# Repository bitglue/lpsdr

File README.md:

# LPSDR

A low performance software defined radio.

Inspired by [HPSDR](http://openhpsdr.org/), except cheaper. Aims to cover HF
bands 160 to 10 meters.

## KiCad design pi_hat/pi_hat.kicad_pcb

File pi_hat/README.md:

# Dual SDR HAT for Raspberry Pi

- Covers all of HF, and probably a little bit of VHF too.
- Two RF inputs, can be tuned independently or coherently.
- LO generated by Si5351. Four outputs are used by the board, the other 4 are
  available on a header.
- [TLV320ADC5140 ADC](http://www.ti.com/lit/ds/symlink/tlv320adc5140.pdf),
  interfaces with Rasberry Pi via I²S.
- Perfboard area for stuff.

The board includes no filters but there is a header where they could be added.

## History

### v0.1 2020-05-14

Initial prototype. Don't know if it works yet.

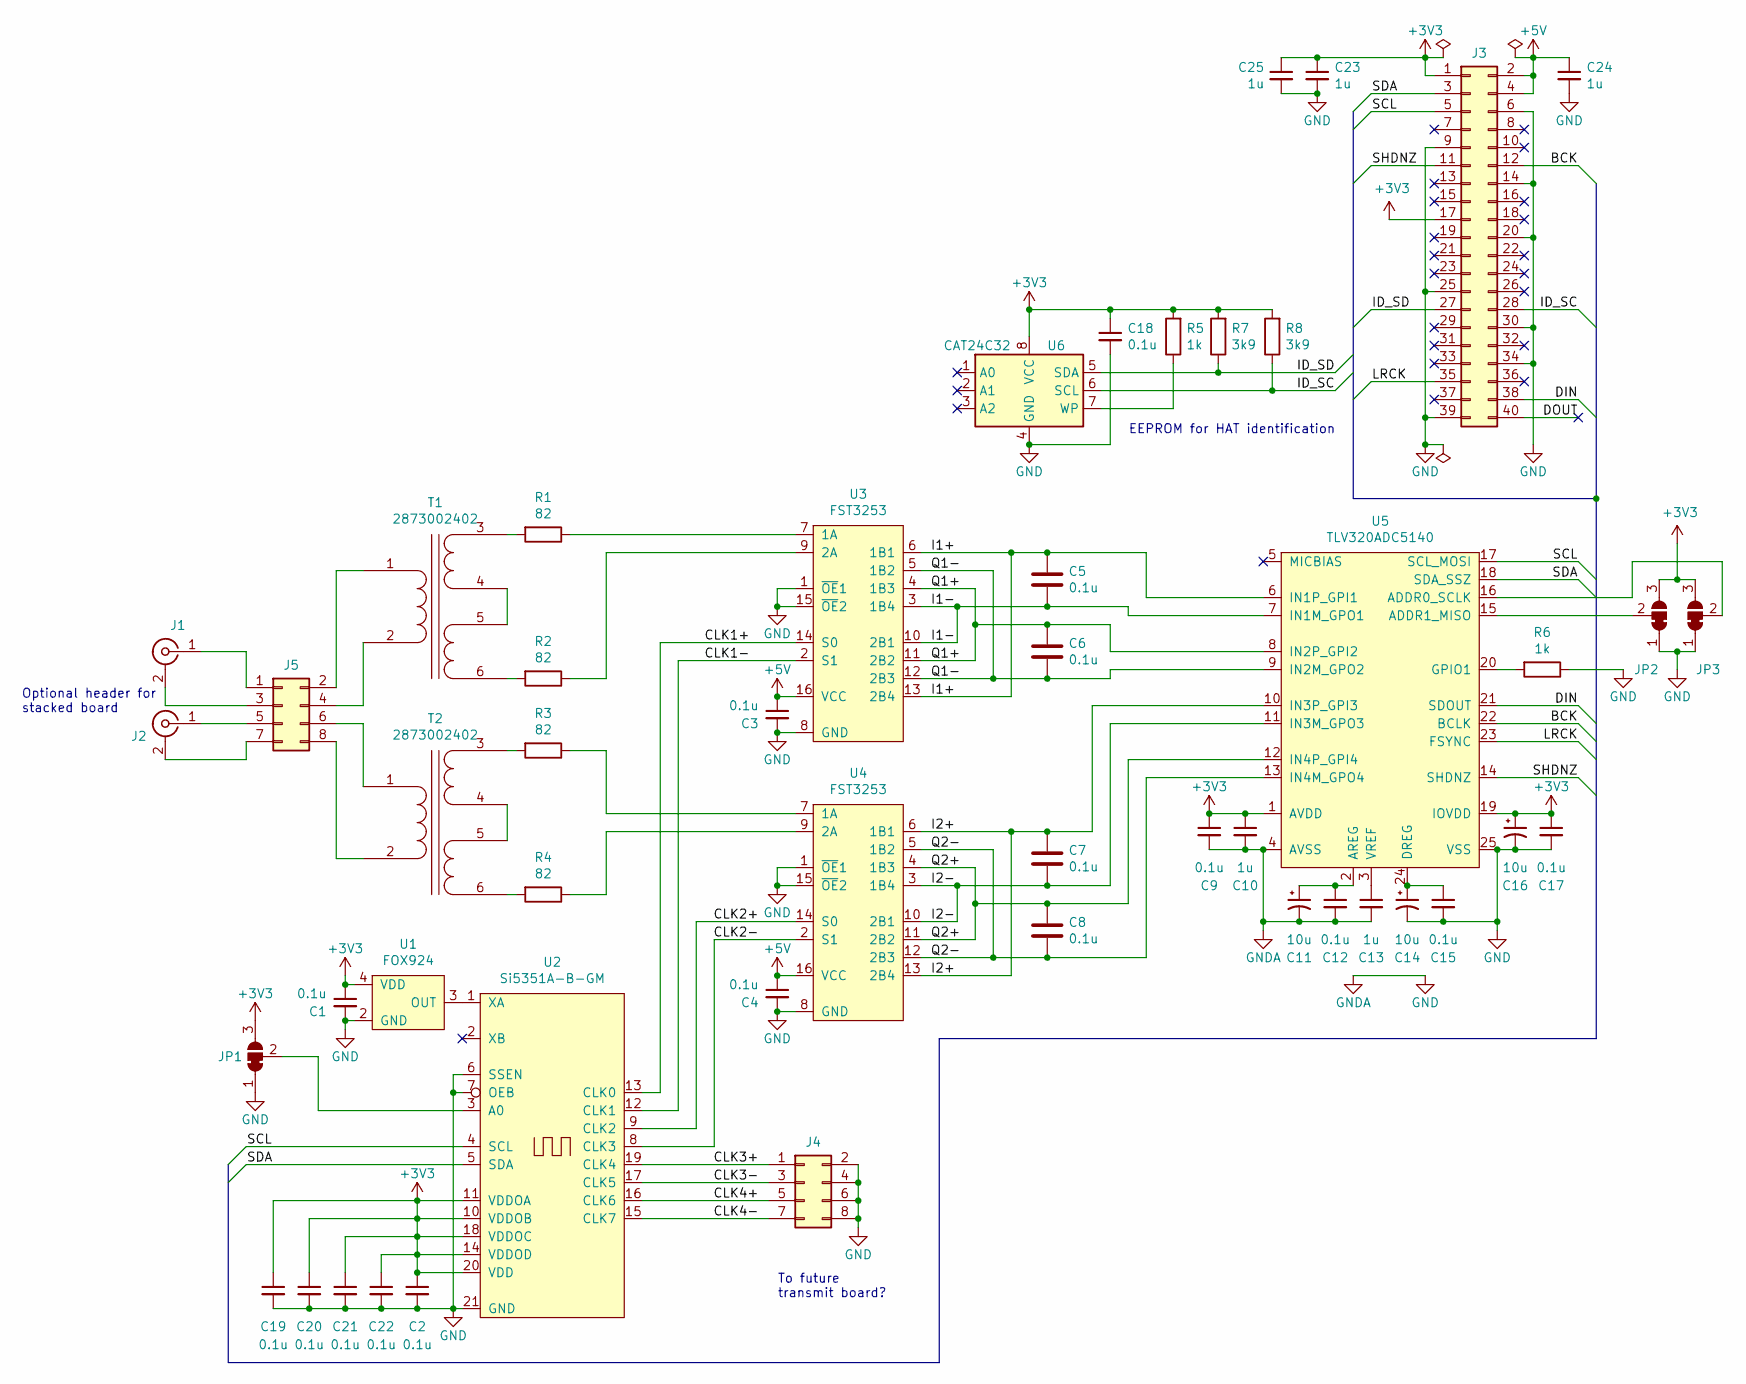
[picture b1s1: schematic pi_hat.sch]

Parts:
C1, C2, C3, C4, C5, C6, C7, C8, C9, C12, C15, C17, C18, C19, C20, C21, C22: 0.1u; C_1206_3216Metric_Pad1.42x1.75mm_HandSolder; mpn C1206C104M5RAC
C10, C13, C23, C24, C25: 1u; C_1206_3216Metric_Pad1.42x1.75mm_HandSolder; mpn C1206C105M3RACTU
C11, C14, C16: 10u; C_1206_3216Metric_Pad1.42x1.75mm_HandSolder; mpn C1206C106M3PAC
J1, J2: Conn_Coaxial; SMA_Samtec_SMA-J-P-H-ST-EM1_EdgeMount; mpn CON-SMA-EDGE-S
J3: Conn_02x20_Odd_Even; Pi_HAT; mpn SSQ-120-03-T-D
J4, J5: Conn_02x04_Odd_Even; PinHeader_2x04_P2.54mm_Vertical
JP1, JP2, JP3: SolderJumper_3_Bridged12; SolderJumper-3_P1.3mm_Bridged2Bar12_RoundedPad1.0x1.5mm
R1, R2, R3, R4: 82; R_1206_3216Metric_Pad1.42x1.75mm_HandSolder; mpn CR1206-FX-82R0ELF
R5, R6: 1k; R_1206_3216Metric_Pad1.42x1.75mm_HandSolder; mpn CRCW12061K00FKEBC
R7, R8: 3k9; R_1206_3216Metric_Pad1.42x1.75mm_HandSolder; mpn CRCW12063K90FKEAC
T1, T2: 2873002402; Binocular_Bifilar_Seconndary; mpn 2873002402
U1: FOX924; Crystal_SMD_EuroQuartz_MJ-4Pin_5.0x3.2mm_HandSoldering; mpn FT5HNBPK27.0-T1
U2: Si5351A-B-GM; QFN-20-1EP_4x4mm_P0.5mm_EP2.25x2.25mm; mpn SI5351A-B-GM
U3, U4: FST3253; SOIC-16_3.9x9.9mm_P1.27mm; mpn FST3253MTCX
U5: TLV320ADC5140; QFN-24-1EP_4x4mm_P0.5mm_EP2.7x2.7mm_ThermalVias; mpn TLV320ADC5140IRTWR
U6: CAT24C32; SOIC-8_3.9x4.9mm_P1.27mm; mpn CAT24C32WI-GT3

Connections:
+3V3: C1.1, C2.1, C9.1, C10.1, C16.1, C17.1, C18.1, C19.1, C20.1, C21.1, C22.1, C23.1, C25.1, J3.1, J3.17, JP1.3 (B), JP2.3 (B), JP3.3 (B), R5.2, R7.2, R8.2, U1.4 (VDD), U2.10 (VDDOB), U2.11 (VDDOA), U2.14 (VDDOD), U2.18 (VDDOC), U2.20 (VDD), U5.1 (AVDD), U5.19 (IOVDD), U6.8 (VCC)
+5V: C3.1, C4.1, C24.1, J3.2, J3.4, U3.16 (VCC), U4.16 (VCC)
/BCK: J3.12, U5.22 (BCLK)
/CLK1+: U2.13 (CLK0), U3.14 (S0)
/CLK1-: U2.12 (CLK1), U3.2 (S1)
/CLK2+: U2.9 (CLK2), U4.14 (S0)
/CLK2-: U2.8 (CLK3), U4.2 (S1)
/CLK3+: J4.1, U2.19 (CLK4)
/CLK3-: J4.3, U2.17 (CLK5)
/CLK4+: J4.5, U2.16 (CLK6)
/CLK4-: J4.7, U2.15 (CLK7)
/DIN: J3.38, U5.21 (SDOUT)
/DOUT: J3.40
/I1+: C5.1, U3.6 (1B1), U3.13 (2B4), U5.6 (IN1P_GPI1)
/I1-: C5.2, U3.3 (1B4), U3.10 (2B1), U5.7 (IN1M_GPO1)
/I2+: C7.1, U4.6 (1B1), U4.13 (2B4), U5.10 (IN3P_GPI3)
/I2-: C7.2, U4.3 (1B4), U4.10 (2B1), U5.11 (IN3M_GPO3)
/ID_SC: J3.28, R8.1, U6.6 (SCL)
/ID_SD: J3.27, R7.1, U6.5 (SDA)
/LRCK: J3.35, U5.23 (FSYNC)
/Q1+: C6.1, U3.4 (1B3), U3.11 (2B2), U5.8 (IN2P_GPI2)
/Q1-: C6.2, U3.5 (1B2), U3.12 (2B3), U5.9 (IN2M_GPO2)
/Q2+: C8.1, U4.4 (1B3), U4.11 (2B2), U5.12 (IN4P_GPI4)
/Q2-: C8.2, U4.5 (1B2), U4.12 (2B3), U5.13 (IN4M_GPO4)
/SCL: J3.5, U2.4 (SCL), U5.17 (SCL_MOSI)
/SDA: J3.3, U2.5 (SDA), U5.18 (SDA_SSZ)
/SHDNZ: J3.11, U5.14 (SHDNZ)
GND: C1.2, C2.2, C3.2, C4.2, C9.2, C10.2, C11.2, C12.2, C13.2, C14.2, C15.2, C16.2, C17.2, C18.2, C19.2, C20.2, C21.2, C22.2, C23.2, C24.2, C25.2, J3.6, J3.9, J3.14, J3.20, J3.25, J3.30, J3.34, J3.39, J4.2, J4.4, J4.6, J4.8, JP1.1 (A), JP2.1 (A), JP3.1 (A), R6.1, U1.2 (GND), U2.6 (SSEN), U2.7 (OEB), U2.21 (GND), U3.1 (~OE~1), U3.8 (GND), U3.15 (~OE~2), U4.1 (~OE~1), U4.8 (GND), U4.15 (~OE~2), U5.4 (AVSS), U5.25 (VSS), U6.4 (GND)
unnamed: C11.1, C12.1, U5.2 (AREG)
unnamed: C13.1, U5.3 (VREF)
unnamed: C14.1, C15.1, U5.24 (DREG)
unnamed: J1.1 (In), J5.1
unnamed: J1.2 (Ext), J5.3
unnamed: J2.1 (In), J5.5
unnamed: J2.2 (Ext), J5.7
unnamed: J5.2, T1.1 (AA)
unnamed: J5.4, T1.2 (AB)
unnamed: J5.6, T2.1 (AA)
unnamed: J5.8, T2.2 (AB)
unnamed: JP1.2 (C), U2.3 (A0)
unnamed: JP2.2 (C), U5.15 (ADDR1_MISO)
unnamed: JP3.2 (C), U5.16 (ADDR0_SCLK)
unnamed: R1.1, U3.7 (1A)
unnamed: R1.2, T1.3 (SA)
unnamed: R2.1, U3.9 (2A)
unnamed: R2.2, T1.6 (SD)
unnamed: R3.1, U4.7 (1A)
unnamed: R3.2, T2.3 (SA)
unnamed: R4.1, U4.9 (2A)
unnamed: R4.2, T2.6 (SD)
unnamed: R5.1, U6.7 (WP)
unnamed: R6.2, U5.20 (GPIO1)
unnamed: T1.4 (SB), T1.5 (SC)
unnamed: T2.4 (SB), T2.5 (SC)
unnamed: U1.3 (OUT), U2.1 (XA)

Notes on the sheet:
To future transmit board?
EEPROM for HAT identification
Optional header for stacked board

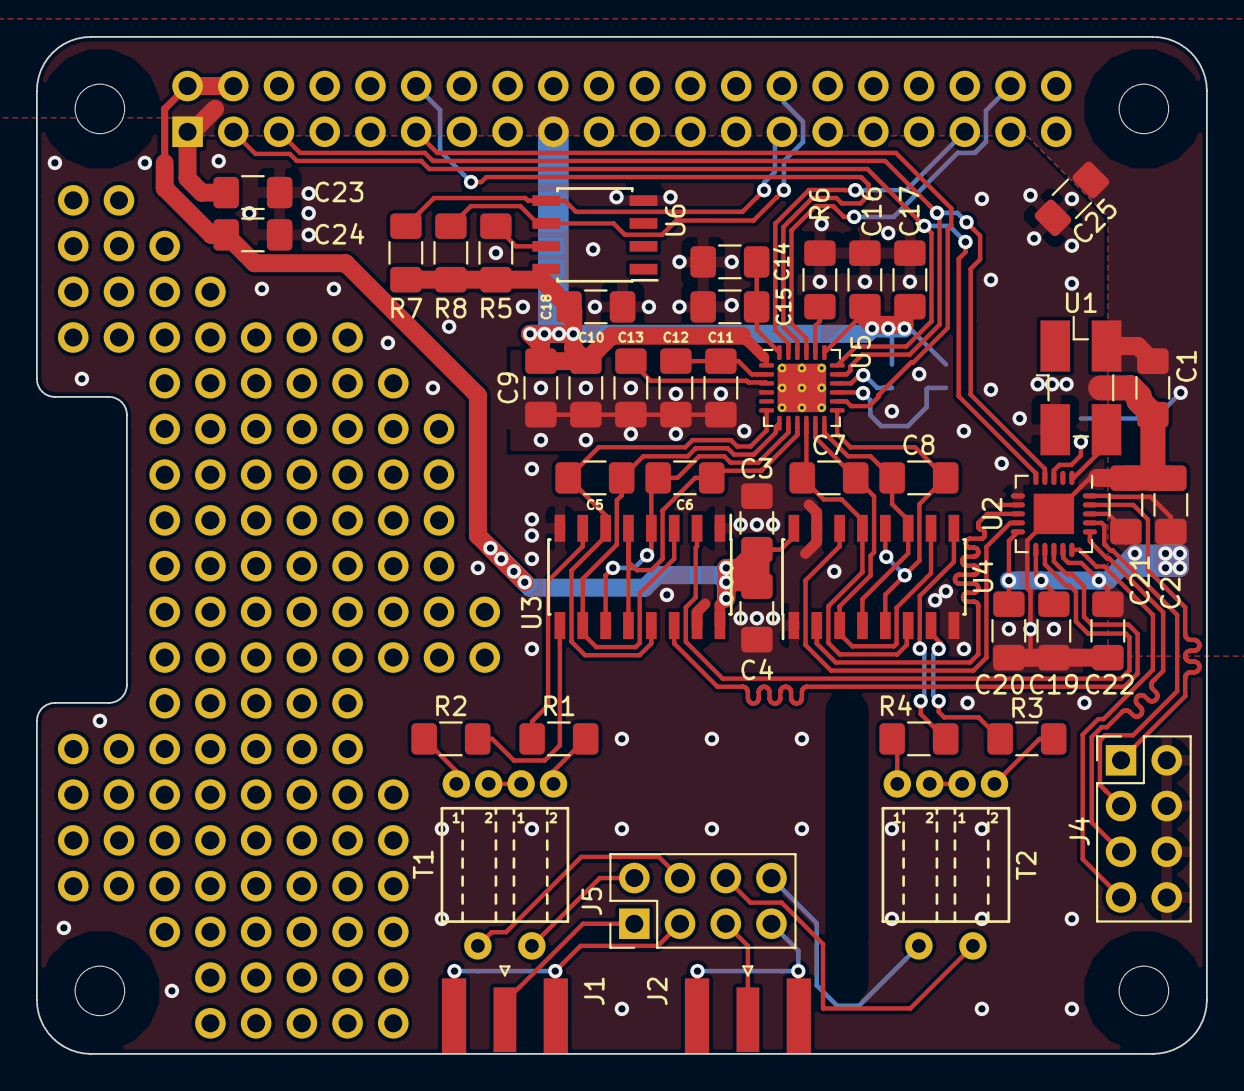
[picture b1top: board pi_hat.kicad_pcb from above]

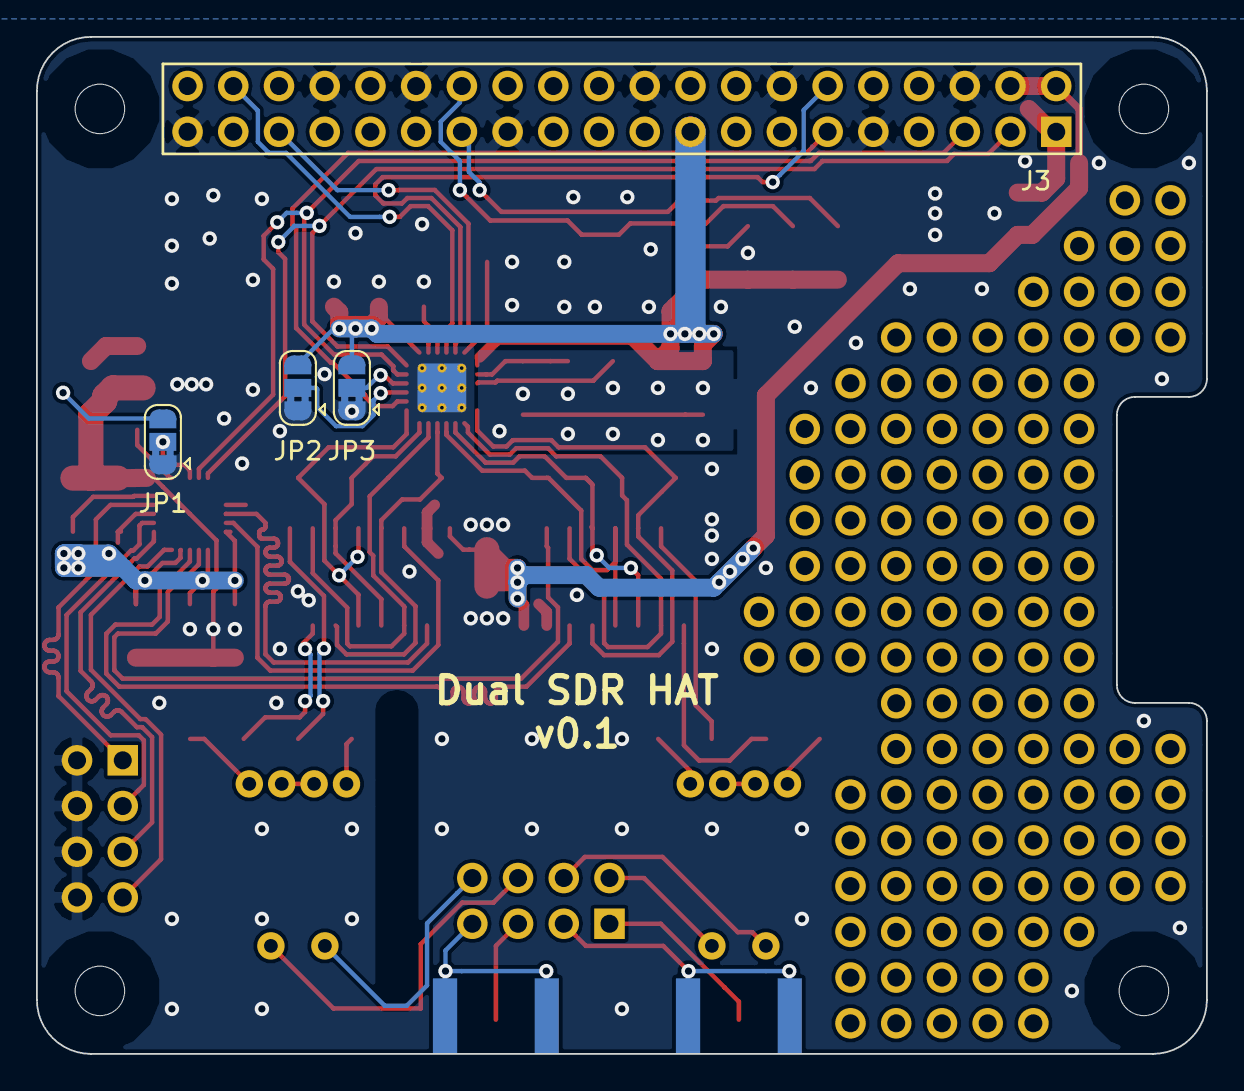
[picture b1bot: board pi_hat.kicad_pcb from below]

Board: 2 copper layers, 65.0 x 56.5 mm, 49 parts (3 on the bottom side), 54 nets.

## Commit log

2017-02-15 Initial revision
    Filter schematic and layout probably good to go, but haven't tested on a
    printed PCB.
    T/R switch mostly done. Needs a few tweaks.
2017-02-17 Tweak T/R relay board
    - Add a Tx LED
    - Add footprints for board-mounted BNC
    - Fix polarity on relay coils
    - Get power and PTT out from 3-pin connector to Pennywhistle
    - Separate RF ground
    Layout is incomplete: decided to incorporate it into a larger relay and
2017-02-17 Add headers to filter board
    These will plug into the T/R relay board, allowing filter modules to be
    easilly swapped.
2017-02-18 Add pluggable filters to T/R board
2017-03-12 Tweak filter layout
2017-12-12 Add relay switched filter selector
2017-12-12 filterboard WIP
2017-12-14 filterboard rough draft
2017-12-18 add footprints, values to filterboard
2017-12-18 begin filterboard layout
2017-12-28 Low-pass filterboard
    Cramming all the filters on one board is too much. Furthermore, it's
    probably better to pair the LP filters with the amplifiers. The PA and
    associated output filters can go in the same box.
2017-12-30 Layout low-pass filterboard
2017-12-30 Work on filterboard layout
2020-05-12 Initial version of Pi HAT
2020-05-13 Add header for external filter board
2020-05-13 Add additional decoupling capacitors
    Si5351 datasheet says we need one per supply pin.
    Also added a couple caps right at the Pi header. Seemed like a good idea
    to limit noise coming on to the board.
2020-05-14 Improve layout after review
    - Move I2C lines from under decoupling cap
    - Beef up power supply traces and add more vias
    - Add another 3.3V bypass cap near the header
    Also, added a .100" grid of plated holes in the unused area, because why
    not.
2020-05-14 Set 2 mil solder mask clearance on QFN packages
    https://docs.oshpark.com/tips+tricks/stop-mask-expansion/
    Other packages are big enough it won't matter.
2020-05-14 Add some brief documentation
2020-05-15 Remove paste from SMA connectors
    These are plenty big to hand-solder, and removing them from the paste
    layer allows for a smaller and thus cheaper stencil.
2020-05-20 Add manufacturer part numbers to schematic
    This works well with KiCost to generate a BOM.
2020-05-20 Update footprints to include 3D models
    Still calling this "v0.1" as the changes should not affect the PCB at
    all.
